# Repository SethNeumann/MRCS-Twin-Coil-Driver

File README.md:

# REPO NAME: MRCS-Twin-Coil-Driver
## License: Creative Commons Attribution-NonCommercial-ShareAlike

Twin Coil Machines present some challenges:

    They tend to slam the points into the stock rails, eventually damaging the connection to the throwbar and the spikes or solder holding the stock rails down 
    can loosen or break.  They make a lot of electrical noise when the power is removed from the coils, which gets into other electronics, causing false operation.
    The coils will overheat and become damaged, if not catch fire, if current is applied for an extended period.
    
    In the past, Capacitive Discharge (CD) supplies were used to make an affordable supply that would protect the coil by not recharging while connected and limiting
    the constant current in case the controls failed and permanently energized the coil.

Our design drives both mild (Atlas, Bachmann, Lifelike, Peco) and "Nasty" PFM, Tenshodo, Ken Kidder, NJ International Twin Coil type machines.  The Twin Coil Driver
(TCD) shapes the pulses driving the switch machines to soften both the physical and electrical blow, reducing electrical noise and physical impact.  Pulse timing is
done in hardware (no chance of a software hang leaving power on).  The TCD works with CD power supplies and modern power supplies such as those used for LEDs, or
inexpensive bench supplies.  

The Twin Coil Driver has internal spike suppression diodes.  Input is logic level and the coils are fired on the rising and falling edge, so a simple toggle switch 
or logic level input controls the machine.

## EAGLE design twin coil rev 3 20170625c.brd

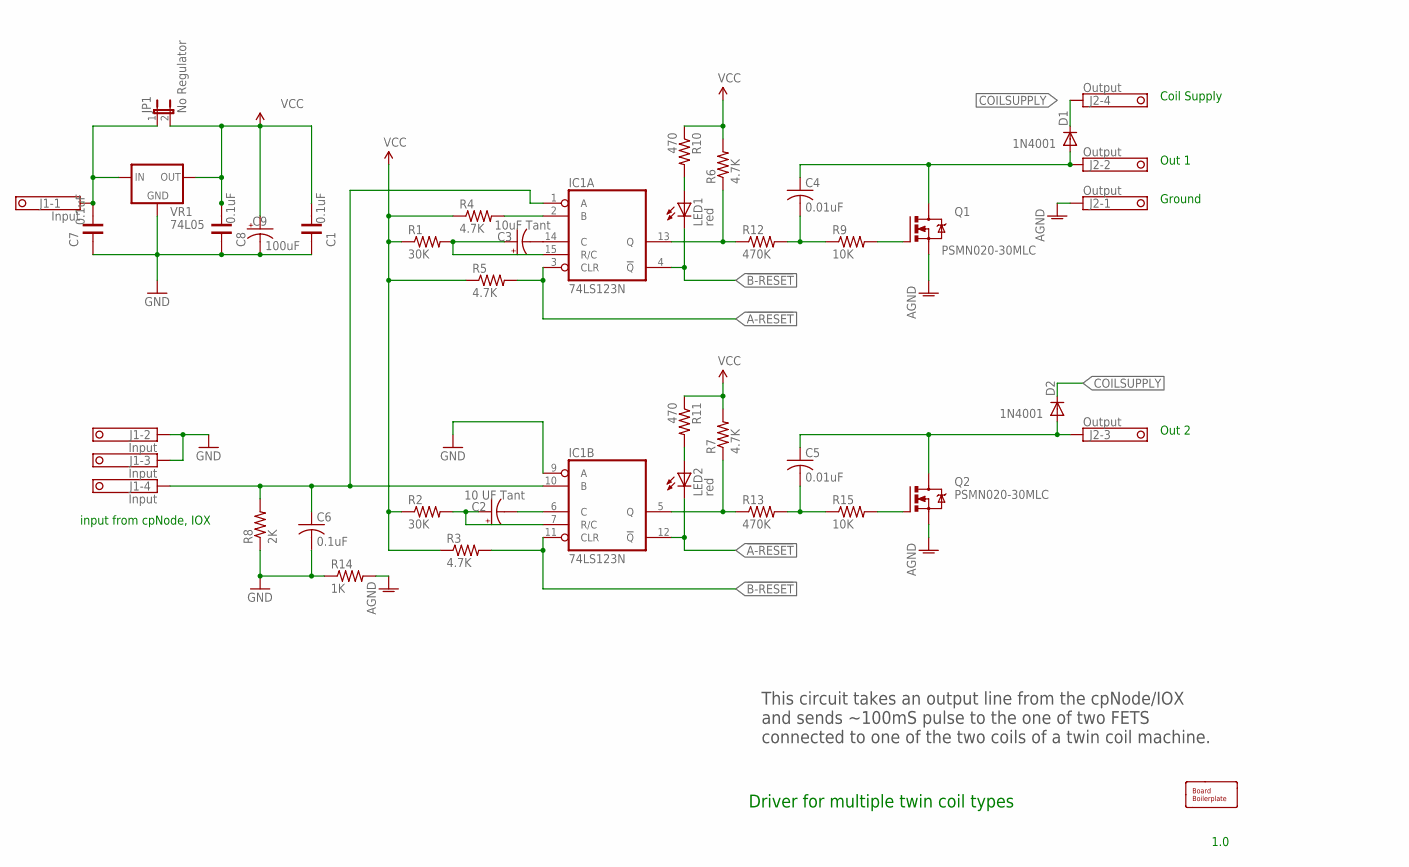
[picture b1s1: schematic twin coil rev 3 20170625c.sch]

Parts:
BOARD1: BOARD69X70; BOARD-DINRAIL-2.7INX7CM
C1, C7, C8: 0.1uF; CAP-PTH-SMALL
C2: 10 UF Tant; E5-4
C3: 10uF Tant; E5-4
C4, C5: 0.01uF; C025-030X050
C6: 0.1uF; C025-030X050
C9: 100uF; E3,5-10
D1, D2: 1N4001; DIODE-1N4001
IC1: 74LS123N; DIL16
J1: Input; 1751264
J2: Output; 1751264
JP1: No Regulator; 1X02_LOCK
LED1, LED2: red; LED3MM
Q1, Q2: PSMN020-30MLC; TO220BV
R1, R2: 30K; AXIAL-0.4
R3, R4, R5, R6, R7: 4.7K; AXIAL-0.4
R8: 2K; AXIAL-0.4
R9, R15: 10K; AXIAL-0.4
R10, R11: 470; AXIAL-0.4
R12, R13: 470K; AXIAL-0.4
R14: 1K; AXIAL-0.4
VR1: 74L05; TO-92

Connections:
!A-RESET: IC1.3 (CLR), IC1.12 (!Q), LED2.K (C), R5.P$2 (2)
!B-RESET: IC1.4 (!Q), IC1.11 (CLR), LED1.K (C), R3.P$2 (2)
AGND: J2.1, Q1.S, Q2.S, R14.P$2 (2)
COILSUPPLY: D1.C, D2.C, J2.4
FETDRIVE1: Q1.G, R9.P$2 (2)
GND: C1.1, C6.2, C7.1, C8.1, C9.-, IC1.8 (GND), IC1.9 (A), J1.2, J1.3, R8.P$1 (1), R14.P$1 (1), VR1.2 (GND)
INPUT: C6.1, IC1.1 (A), IC1.10 (B), J1.4, R8.P$2 (2)
unnamed: IC1.13 (Q), R6.P$1 (1), R12.P$1 (1)
unnamed: IC1.5 (Q), R7.P$1 (1), R13.P$1 (1)
unnamed: Q2.G, R15.P$2 (2)
unnamed: IC1.2 (B), R4.P$2 (2)
unnamed: C3.-, IC1.14 (C)
unnamed: C2.-, IC1.6 (C)
unnamed: C3.+, IC1.15 (R/C), R1.P$2 (2)
unnamed: C2.+, IC1.7 (R/C), R2.P$2 (2)
unnamed: C4.2, R9.P$1 (1), R12.P$2 (2)
unnamed: C5.2, R13.P$2 (2), R15.P$1 (1)
unnamed: LED1.A, R10.P$2 (2)
unnamed: LED2.A, R11.P$2 (2)
OUT1: C4.1, D1.A, J2.2, Q1.D
OUT2: C5.1, D2.A, J2.3, Q2.D
V+: C7.2, J1.1, JP1.1, VR1.3 (IN)
VCC: C1.2, C8.2, C9.+, IC1.16 (VCC), JP1.2, R1.P$1 (1), R2.P$1 (1), R3.P$1 (1), R4.P$1 (1), R5.P$1 (1), R6.P$2 (2), R7.P$2 (2), R10.P$1 (1), R11.P$1 (1), VR1.1 (OUT)

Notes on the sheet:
input from cpNode, IOX
This circuit takes an output line from the cpNode/IOX and sends ~100mS pulse to the one of two FETS connected to one of the two coils of a twin coil machine.
Coil Supply
Out 2
Out 1
Ground
Driver for multiple twin coil types
1.0

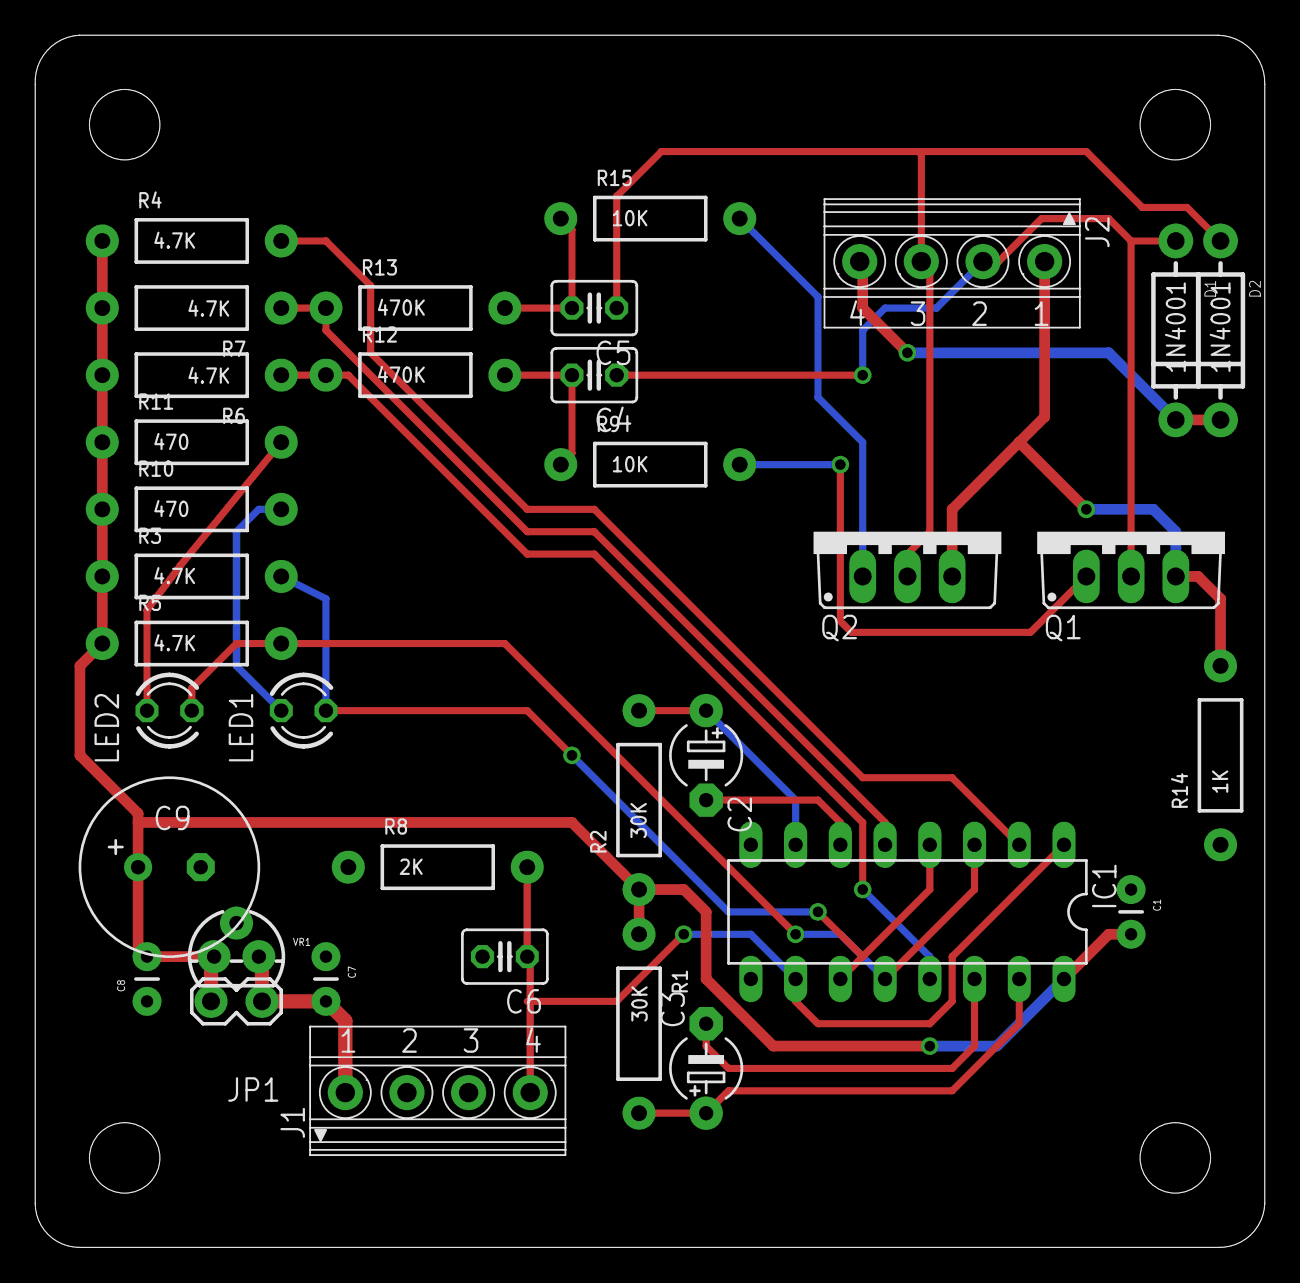
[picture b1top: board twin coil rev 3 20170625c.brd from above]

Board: 2 copper layers, 69.8 x 68.8 mm, 38 parts (0 on the bottom side), 23 nets.

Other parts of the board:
U$1: CA-PROP65WARNING
U$2: MRCSLOGOTOP

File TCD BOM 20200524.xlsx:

Qty | Value | Device | Package | Parts | Description | MRCS | Jameco | OC_NEWARK | Banggood | Digikey | Leads | Leads Extd | unit | Extd | EOQ
1 |  | BOARD69X70 | BOARD-DINRAIL-2.7INX7CM | BOARD1 |  | TOB-BB |  |  |  |  |  | 0 | 1 | 1 | 5
2 | .022 uF | C-US025-030X050 | C025-030X050 | C4, C5 | CAPACITOR Monolithic .022 @ 50V 223 |  | 2306383 |  |  |  | 2 | 4 | 0.15 | 0.3 | 100
4 | 0.1uF | C-US025-030X050 | C025-030X050 | C1, C6, C7, C8 | Capacitor - Monolithic 0.1 (104) @ 50V |  | 2295911 |  |  |  | 2 | 8 | 0.02 | 0.08
2 | 10 UF Tant | CPOL-USE5-4 | E5-4 | C2, C3 | POLARIZED CAPACITOR, American symbol |  |  |  |  |  | 2 | 4 | 0.45 | 0.9 | 20
1 | 100uF | CPOL-USE3.5-10 | E3,5-10 | C9 | POLARIZED CAPACITOR, American symbol |  | 29962 |  |  |  | 2 | 2 | 0.16 | 0.16 | 10
1 | 1K | RESISTORPTH-1/4W | AXIAL-0.4 | R14 | Resistor 1K 1/4W |  | 690865 |  |  |  | 2 | 2 | 1.2E-2 | 1.2E-2 | 100
2 | 10K | RESISTORPTH-1/4W | AXIAL-0.4 | R9, R15 | Resistor 10K 1/4W |  | 691104 |  |  |  | 2 | 4 | 0.01 | 0.02 | 100
2 | 1N4001 | DIODEPTH | DIODE-1N4001 | D1, D2 | Diode 1N4004 |  | 35991 |  |  |  | 2 | 4 | 0.06 | 0.12 | 100
3 | 2K | RESISTORPTH-1/4W | AXIAL-0.4 | R8, 10,11 | Resistor 2K 1/4W |  | 690865 |  |  |  | 2 | 6 | 0.02 | 0.06 | 100
2 | 30K | RESISTORPTH-1/4W | AXIAL-0.4 | R1, R2 | Resistor 30K 1/4W |  | 691219 |  |  |  | 2 | 4 | 0.02 | 0.04 | 100
5 | 4.7K | RESISTORPTH-1/4W | AXIAL-0.4 | R3, R4, R5, R6, R7 | Resistor 4.7K 1/4 W |  | 691024 |  |  |  | 2 | 10 | 0.02 | 0.1 | 100
2 | 470K | RESISTORPTH-1/4W | AXIAL-0.4 | R12, R13 | Resistor, 470K 1/4W |  | 691500 |  |  |  | 2 | 4 | 0.01 | 0.02 | 100
1 | 78L05 | V_REG_78L05 | TO-92 | VR1 | Voltage Regulator |  | 51182 |  |  |  | 3 | 3 | 0.25 | 0.25 | 100
1 | 74LS123N | 74LS123N | DIL16 | IC1 | Retriggerable monostable MULTIVIBRATOR |  | 46480 |  |  |  |  | 0 | 0.79 | 0.79 | 10
2 | Input, output | 4 pos 3.5mm screw | 4 pos 3.5mm screw | J1, J2 | MKDS 1/ 4-3,5 Printklemme |  | 2124411 | 10R0934 |  |  | 4 | 8 | 0.49 | 0.98 | 100
1 | socket | 16 pin DIP | 16 pin DIP | IC1-s | 16 pin DIP socket |  | 112222 |  |  |  | 16 | 16 | 0.13 | 0.13 | 100
1 | No Regulator | JUMPER-2PTH_LOCK | 1X02_LOCK | JP1 | Jumper |  |  |  | X |  | 2 | 2 | 0.02 | 0.02 | 4000
2 | PSMN020-30MLC | STP5NA50 | TO220BV | Q1, Q2 | N-CHANNEL MOS FET |  | 787798 |  | X |  | 3 | 6 | 0.59 | 1.18 | 100
1 | red | LED3MM | LED3MM | LED1 | LED Green |  |  |  | X |  | 2 | 2 | 0.01 | 0.01 | 300
1 | green | LED3MM | LED3MM | LED2 | LED Red |  |  |  | X |  | 2 | 2 | 0.01 | 0.01 | 300
 | BOM Cost |  |  |  |  |  |  |  |  |  |  | 91 |  | 6.1819999999999995
 | BOM Markup | 0.2 |  |  |  |  |  |  |  |  |  |  |  | 1.2363999999999999
 | BOM Subtotal |  |  |  |  |  |  |  |  |  |  |  |  | 7.4183999999999992
 | Labor @ | 0.2 | per lead |  |  |  |  |  |  |  |  |  |  | 18.2
 | Labor Markup | 0.2 |  |  |  |  |  |  |  |  |  |  |  | 3.64
 | Labor Subtotal |  |  |  |  |  |  |  |  |  |  |  |  | 21.84
 | Cost Total |  |  |  |  |  |  |  |  |  |  |  |  | 29.258399999999998
 | e-Commerce | 0.1 |  |  |  |  |  |  |  |  |  |  |  | 2.92584
 | Grand Total |  |  |  |  |  |  |  |  |  |  |  |  | 32.184239999999996
 | Sell |  |  |  |  |  |  |  |  |  |  |  |  | 32

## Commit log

2021-02-22 initial commit
    initial commit
2021-02-22 intial commit
2021-02-22 intial commit
    from the old EAGLE Directory
2021-02-22 deleted template files
    deleted files from template, using working files from EAGLE
2021-02-22 First pass at documentation
    quick start
2021-02-23 Initial Commit
    User Manual
2021-02-23 Minor typo corrections and clarifications
    changes for readibility

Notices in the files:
parts and their libraries:
SparkFun-Passives: Licensing: CC v3.0 Share-Alike You are welcome to use this library for commercial purposes.
SparkFun-PowerIC: Licensing: Creative Commons ShareAlike 4.0 International - https://creativecommons.org/licenses/by-sa/4.0
